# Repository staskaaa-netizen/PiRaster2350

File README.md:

# PiRaster

**PiRaster** is the RP2350/LVDS pixel backend that was written inside uCNC, on
its own: panel timing and scanout, a 4bpp indexed framebuffer, a sixteen-colour
palette, and the drawing primitives every screen is built from. It drives one
panel - a **Sharp LQ121S1LG44**, 800x600, single-channel LVDS, mounted turned a
quarter - and it has been on that panel and no other. The repository is
`PiRaster2350`, after the chip it drives.

It **began as a fork of [PicoLVDS](https://github.com/ceteras/PicoLVDS)**, and
then turned into something much different: what survives from that project is a
handful of its ideas - the HSTX pacer LUT and the way a scanline is packed among
them - while the scanout, the SRAM framebuffer and its palette, the drawing core,
the fonts and the target seam underneath all of it are this project's own. Those
ideas are PicoLVDS's, and the credit for them is that project's.

It was extracted from
`uCNC/src/modules/lvds_renderer` (see *Where this came from* below). The drawing
code, the palette and the fonts are the same code; the hardware half stopped
including `cnc.h` and calls four port hooks instead.

## What you can do with it

Use PiRaster for a **simple panel with a fast and stable picture**:

* **Text where you want it.** `lvds_draw_text(x, y, ...)` writes a string at any
  view coordinate, in three sizes - 6x8 condensed, 8x14, and 8x14 doubled - and
  in any colour of the current palette. Each glyph carries its own background
  colour, because a glyph is filled rectangles. `lvds_draw_text_clip()` writes
  the same text in a fixed number of columns, so the rows of a screen line up
  without the caller measuring anything.
* **A big, cheap screen.** 800x600 is a large work area for text and boxes, and
  a panel of this class costs little. The upright view holds 133 columns by 75
  rows of the 6x8 face, 100 by 42 of the 8x14, and 50 by 21 of the doubled one.
* an operator screen for a machine: text, lines, rectangles and filled
  rectangles in sixteen colours;
* **Motion when you want it.** Lines, rectangles and ellipses animate as well as
  they draw. The sample scene moves a wave, a disc and a gauge from the clock.
  The operator panel is the main job of this path, and motion is the extra.
* a state that you show with a colour, because you can change a palette slot
  while the picture runs;
* a picture that a client makes itself - an emulator, a game, a picture pump -
  because `lvds_target_blit()` takes one row of indices at a time;
* the same picture on a desk, because the host target writes BMP frames and the
  project checks the pixels.

## What you cannot do with it

PiRaster is not a modern display path. Read the limits before you start:

* **Sixteen colours.** The frame uses 4 bits for each pixel. There is no
  blending, no alpha, no anti-aliasing and no image scaling.
* **No video and no photographs.** The path has no decoder and no scaler.
* **One panel and one board.** The geometry, the timing and the clocks are
  compiled in for a Sharp LQ121S1LG44 on an RP2350.
* **No compositor.** There are no layers and no rotation of arbitrary content.

For a modern panel, use its own DSI, eDP or HDMI path.
[docs/when-to-use.md](docs/when-to-use.md) gives the full comparison.

## Features

* **A stable picture.** The default build draws into a PSRAM backbuffer, then
  copies the frame into the scanout buffer. The scanout never reads a
  half-drawn picture.
* **A live palette.** You can re-colour a slot while the picture runs. Everything
  that already uses that colour changes on the next prepared line. You do not
  redraw the screen, and you do not lose a slot.
* **The turn in one place.** The build states the panel mounting one time, in
  `core/lvds_view.h`. Text, lines, rectangles and ellipses then turn with it.
* **A blit call for a client raster.** A client that makes its own rows of
  palette indices draws at row speed, not at pixel speed.
* **A host target.** The same drawing code writes the same picture into a frame
  in RAM, so you can check a layout without a board.
* **Four spare active lines.** The frame carries 604 active lines, not 600. The
  panel shows one line twice at the close of the active area. The four spare
  lines give that repeated line its own place, away from the picture. This is a
  feature of the panel support; the fault behind it is a known issue.
* **Static realtime memory.** The scanout memory is static, aligned and in SRAM.
  The scanout path has no allocator.

## Known issues

* **The panel repeats one line at the close of the active area.** The root cause
  is not known. The four spare active lines hold the repeated line away from the
  picture. **Do not shorten the frame.** The measurements are in
  [LIMITS.md](LIMITS.md). The record is in
  [docs/torture-history.md](docs/torture-history.md).
* **One clock point gives no video.** `420000 / div 3` produces no picture. This
  is a limit of this board. It is not a requirement of the panel.
* **A full redraw costs 33 ms** in the default (double buffered) build. The
  single buffered build costs 3 ms, but the picture tears.
* **The host samples do not run on this bench machine.** Its MinGW gcc cannot
  run its own cc1. The samples compile, and `make run` runs them on a machine
  with a working compiler.

## License

PiRaster is free software under the **GNU General Public License, version 3**
(see [LICENSE](LICENSE)). PiRaster began as a fork of
[PicoLVDS](https://github.com/ceteras/PicoLVDS). That project is also GPL-3.0,
and the ideas that PiRaster keeps from it stay under the same license.

## The boundaries

```
  core/                    device independent. No SDK, no OS, no threads.
    lvds_color.h           a colour: 5-6-5, or a palette slot once a target has one
    lvds_view.h            the view <-> panel turn, stated once
    lvds_canvas.{h,c}      the surface: the only two calls that write, + guards
    lvds_draw.{h,c}        lines, rectangles, ellipses, text (built on those two)
    lvds_palette.{h,c}     the sixteen named colours
    lvds_font*.{h,c}       the two bitmap faces
    lvds_target.h          the seam: what a target implements
  panels/
    sharp_lq121s1lg44.h    geometry, timing, pins and clocks, as data
  targets/
    host/                  the panel on a desk: a 32bpp frame in RAM + a BMP writer
    rp2350/                the panel itself: HSTX, DMA, core1, PSRAM, the port
  samples/
    common/scene.{h,c}     the one picture every sample draws, and the palette banks
    host_loop/             a while loop that draws and writes frames
    host_snapshot/         one frame, checked pixel by pixel - a sample that is a test
    rp2350_panel/          the same picture, on the glass
  lvds_config.h            which panel this build drives
```

Two rules hold the split together:

* **Everything above `lvds_target.h` is portable.** It never mentions DMA, HSTX,
  PSRAM, a pin, or whether the picture ends up on glass or in a file.
* **Everything below it is one panel on one board.** A target writes pixels,
  presents, and owns the palette. It never mentions the view, the turn, the
  palette's names or the drawing primitives.

The documents behind it:

* [docs/architecture.md](docs/architecture.md) - what each layer does with a
  frame, the scanout chain step by step, and the numbers it runs at;
* [docs/boundaries.md](docs/boundaries.md) - who owns what, and why the split is
  where it is;
* [docs/when-to-use.md](docs/when-to-use.md) - what it is good for, what it is
  not, and what to use instead for a modern panel;
* [docs/torture-history.md](docs/torture-history.md) - the stress harness, the
  retired workarounds, and the faults and measurements behind them;
* [LIMITS.md](LIMITS.md) - the hardware limits a consumer has to know before
  using it somewhere new, and what still needs the bench.
* [hardware/](hardware/README.md) - the adapter: its schematic, the KiCad
  project, the fabrication files, and the eight HSTX pins this build drives.

The panel is drawn **upright by default**. A glass bolted turned a quarter -
the machine's own mounting - is one build flag (`-DLVDS_PANEL_TURN=90`, see
`platformio.ini`), and the layout follows it.

**The palette is live.** A colour's name can be redefined while the picture
runs (`lvds_palette_define()`): on the glass the slot it already holds is
re-coloured in place, so everything drawn in that colour changes with it on the
next scanline, with no redraw and no slot churn. `scene_palette_switch()` in the
samples walks four banks to show it.

## Hardware

| what | this build |
| --- | --- |
| glass | Sharp LQ121S1LG44, 800x600, single-channel LVDS: three data pairs and one clock pair |
| board | Waveshare RP2350-PiZero (`-D PICO_BOARD=\"waveshare_rp2350_pizero\"`) |
| HSTX pairs | D0+ D0- D1+ D1- D2+ D2- CLK+ CLK- = GP12, GP13, GP14, GP15, GP16, GP17, GP18, GP19 |
| carrier | the PicoLVDS LVDS adapter, carried in [hardware/](hardware/README.md) |

**There is no LVDS transmitter chip.** The RP2350's HSTX serialiser drives the
panel's four LVDS pairs from those eight pins, in the seven-phase packing that
the pacer LUT produces. That is the idea PiRaster took from PicoLVDS, and it is
the reason this display path is a header of numbers plus one target.

The design of the adapter - schematic, KiCad project and fabrication package -
lives in [hardware/](hardware/README.md), where the project this one came from
keeps it. The eight pins are stated for the firmware in
`panels/sharp_lq121s1lg44.h`, which is the only place the code reads them.

## Build and run

**The host samples need a C compiler and make, nothing else.**

```console
make            # builds both host samples
make run        # builds them, draws three frames, checks one and writes BMPs
```

`samples/host_snapshot/` exits non-zero when a pixel is not where the scene put
it, so `make run` is also a check. The BMPs are written the way the operator
reads the glass: the frame is 800x600 landscape, the picture is 600x800 and
turned, and `host_panel_write_bmp(path, true)` turns it back for you.

**The firmware sample is a PlatformIO project** (`pio run -e rp2350_panel`),
because that is the stack the panel was brought up on; the UF2 lands in
`.pio/build/rp2350_panel/firmware.uf2`. `samples/rp2350_panel/main.cpp` is
Arduino style: `setup()` brings the panel up, and `loop()` draws the scene and
presents it. The framework's own `main()` is `while (1) { loop(); }`, so the
sample adds nothing to it but those calls. The loop paces itself with `millis()`
(`FRAME_MS`, about 50 frames a second), and the drawing itself is a function of
that clock, so the demo behaves the same on every build.

`pio run -e rp2350_panel_fps -t upload` is the same sample with its **frame
meter** in: the loop runs flat out and every sixty frames it prints the
milliseconds a whole frame - clear, scene, present - takes. That is how the
project answers "is this fast enough for a game", on the panel, rather than
guessing from datasheets.

Two meters, because the answer depends on where the draw buffer lives:
`rp2350_panel_fps` uses the double-buffered PSRAM path (the default, and the
machine's), and `rp2350_panel_sram_fps` draws straight into the scanout buffer
for the fast, tearing comparison. A serial terminal must assert DTR
(`pio device monitor` does; a bare port read may not) or the board's output is
dropped.

**The console is the USB serial port, 115200 8N1.** The port appears when the
application runs, and on this bench the application does not run until RESET is
pressed (below). `pio device list` shows its number, and the number can change
between uploads.

```console
pio device list                        # find the port (USB VID:PID 2E8A:...)
pio device monitor -p COM13 -b 115200  # read it
```

The framework drops CDC output until the host asserts DTR, and
`pio device monitor` asserts it. A monitor that is opened after the board has
started would therefore miss the boot lines, so `console_announce()` in the
sample says the state again for each terminal that attaches. `lvds: draw buffer
in psram` is the line to look for; `lvds: the panel did not come up` replaces it
when the bring-up failed.

**A build that prints checks that someone is listening.** The framework's
`Serial` write has nothing to do when no host is attached, so the sample asks
`Serial` (the connected flag) before writing, in both the frame meter and the
port's log hook. What an unwatched write does to this board was *not*
established: a meter build disappearing from the USB bus turned out to be the
reset below, not the write. The announce line follows the same rule: it is
written only while the connected flag is set.

**Flashing on this board: press RESET after the upload.** `pio run -t upload`
does its job - it resets the board into BOOTSEL, writes the image and verifies
it - but the tool's own reboot into the application often does not bring it up
here, and the board sits with no port until the RESET button is pressed. The
board can also drop off the bus with no upload involved at all. The cause is not
established; the measurements, the candidate cause and the recovery checklist
are in [docs/torture-history.md](docs/torture-history.md). One thing is
established: no watchdog inside the firmware can cover that state, because the
firmware is not running in it.

**The default is double buffered on purpose.** Drawing straight into the buffer
the scanout is reading is several times faster, but the panel is looking at the
picture while it is half redrawn - a screen clear per frame reads as a flicker -
which is the lesson LeanCam already learned. Single buffering is an explicit
choice, never the default.

The samples have no RTOS, no tasks, no callbacks and no state machines: draw,
present, repeat. `samples/common/scene.c` is the whole demo, and it is the same
file for the desk and for the glass.

### Native packed-colour builds

`rp2350_panel_4color` runs the original 800x600 PiRaster scene through the
normal core1 and 7x256 LUT scanout, but packs four pixels into each framebuffer
byte:

```console
pio run -e rp2350_panel_4color -t upload
```

All named scene colours map onto black, white, green and blue. The framebuffer
is 120,800 B instead of 241,600 B, and the complete build uses 177,900 B of
RAM with 345,320 B of heap left. The operator saw the native 800x600
four-colour scene run stably on the glass.

Core1 still produces the same seven-phase LVDS words. A 256-entry expansion
table turns each packed 2bpp byte into four nibble indices before the existing
colour LUT. This keeps the unpack work short enough for the scanline deadline.

The green monochrome variant packs eight pixels per byte:

```console
pio run -e rp2350_panel_1bpp -t upload
```

It maps the scene onto black and one green foreground. The framebuffer is
60,400 B and the complete build uses 117,996 B of RAM with 405,224 B of heap
left. A 256-entry table expands each byte directly to all eight nibble indices.
The operator saw the native 800x600 green scene on the glass after the board's
usual post-upload reset.

### CPU-less Command Expander bench

The SRAM-resident line-stream probe works on the glass. It proves that the
HSTX Command Expander can carry the existing raw LVDS words without core1
preparing scanlines.

```console
pio run -e rp2350_panel_headless_sram_bars -t upload
```

The probe bakes three command streams in SRAM: one active colour-bar line, one
blank line, and one VSYNC line. The DMA descriptor ring reuses them for the
frame. The ring has 1,024 entries, so its 354 guard lines lengthen vertical
blanking and lower refresh to about 37 Hz. This is a mechanism probe, not a
panel-timing configuration.

The same mechanism now carries a full-screen, four-colour source:

```console
pio run -e rp2350_panel_headless_200x120 -t upload
```

The source is **200x120**, stored in 12,000 B of SRAM. Every source row is
expanded once through the palette and 7x256 LUT, then nearest-neighbour scaled
4x horizontally and 5x vertically to fill 800x600. Each scaled row is stored as
one complete 925-word scanline, so the 120 rows use 444,000 B. One HSTX-paced
data channel and one descriptor channel loop the rows; core1 remains idle. The
build uses 488,300 B of static RAM, leaving 33,576 B of heap.

Core0 may redraw and rebuild the rows only after descriptor 669. The 354 guard
lines plus the start of vertical blanking give about 9.3 ms, enough for the
four-colour scene at 10 fps. Core1 remains idle. The operator saw the scene
animate on the glass without tearing.

The palette is part of the bake. A colour change does not reach a running
headless stream; the picture must be baked again. The live palette is therefore
lost in this mode.

**`RAW_REPEAT` does not make an LVDS colour line tiny.** A constant-colour
LVDS line still produces seven distinct 32-bit phase windows, and the command
expander repeats one word sequentially. Reordering those seven phases into
seven repeated runs would change the stream. The probe therefore uses complete
`RAW` lines. `RAW_REPEAT` is only correct where a run really consists of
consecutive equal raw words.

The full-frame PSRAM variant is retired:

* its first colour-bar build produced no video;
* a second build produced blinking, never a static frame;
* the working SRAM probe isolates the failure to the PSRAM full-frame loop,
  not the raw LVDS command words.

The scene snapshot was therefore not attempted. The normal core1 path remains
the only supported full-frame scanout. The rollback baseline is the uCNC NCC
image:

```console
pio run -e RP2350-LEANCAM-LVDS-NCC -t upload
```

## What has been verified, and what has not

Verified here:

* `pio run -e rp2350_panel` builds the firmware sample and links it
  (RAM 56.8%, flash 0.4% of 16 MB, `firmware.uf2` generated).
* The normal build is unchanged at RAM 298,156 B and flash 84,824 B after the
  bake API was extracted from the same active-line routine.
* The native four-colour 2bpp build links at RAM 177,900 B and flash 84,760 B.
  The operator saw its 800x600 scene run stably.
* The green 1bpp build links at RAM 117,996 B and flash 84,704 B. The operator
  saw its native 800x600 scene on the glass.
* `rp2350_panel_headless_sram_bars` builds and links at RAM 295,392 B and flash
  70,384 B.
* `rp2350_panel_headless_200x120` builds and links at RAM 488,300 B and flash
  82,992 B.
* The headless ELF has no `core1_entry` or `poll_dma_scanout` symbol.
* The operator saw the SRAM-resident colour bars on the panel with core1 idle.
  This is hardware-verified: the raw Command Expander path and the SRAM line
  reuse work.
* The operator saw the 200x120 four-colour scene full-screen and animating on
  the panel. This hardware-verifies the integer-scaled SRAM line mode and the
  blank-window row rebuild.
* The portable half - core, host target and both host samples - compiles
  warning-free under `-Wall -Wextra` with the toolchain's ARM compiler.

Not verified here:

* **The full-frame PSRAM scanout remains negative.** The 2,479,000-byte loop
  produced no video, then blinking; it never produced a static frame. It stays
  retired.
* **The native-resolution scene comparison was not attempted.** The PSRAM
  scene path failed, and a complete native-resolution scene does not fit the
  SRAM-resident line mechanism. The 200x120 mode is a separate low-resolution
  probe.
* **The host samples have not been run on this machine.** Its MinGW `gcc` cannot
  run its own `cc1` (missing prerequisite DLLs), so any host build fails before
  compiling a line. `make run` is one command away on a machine whose compiler
  works; the check inside `host_snapshot` is what makes that run meaningful.
* The normal demo and the SRAM-resident bars have been on the glass. The
  frame-close tail and the full list of clock points still need their own bench
  checks, listed in `LIMITS.md`.

## Where this came from

`uCNC/src/modules/lvds_renderer` is the same renderer inside uCNC, and the
same directory - module and library, one copy - was published to the
`uCNC-modules` repository. This project is that code rearranged around a target
seam, with the four uCNC calls (`mcu_millis`, `cnc_delay_ms`, `proto_info`,
`cnc_is_file_io_critical`) replaced by `targets/rp2350/rp2350_port.h`.

**The two copies can drift.** They are the same code today; when this project
becomes the owner, the module should be generated from it or replaced by it
rather than edited beside it. That decision has not been made yet.

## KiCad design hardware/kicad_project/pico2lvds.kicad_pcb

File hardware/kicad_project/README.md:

# LVDS adapter

Tested with B089AW01-V.0 and HSD089IFW1-A00-V1.0 on a breadboard.
I'm sure it will work with other displays from old netbooks.

This pcb was not tested yet!

Do NOT build if you're not confident in debugging electronics.
The LVDS cable needs to be hand made, there is no commercially available cable with this layout.
I plan to build mine using the cable from the original netbook, if and when I'll get the pcb ordered.

Good luck!

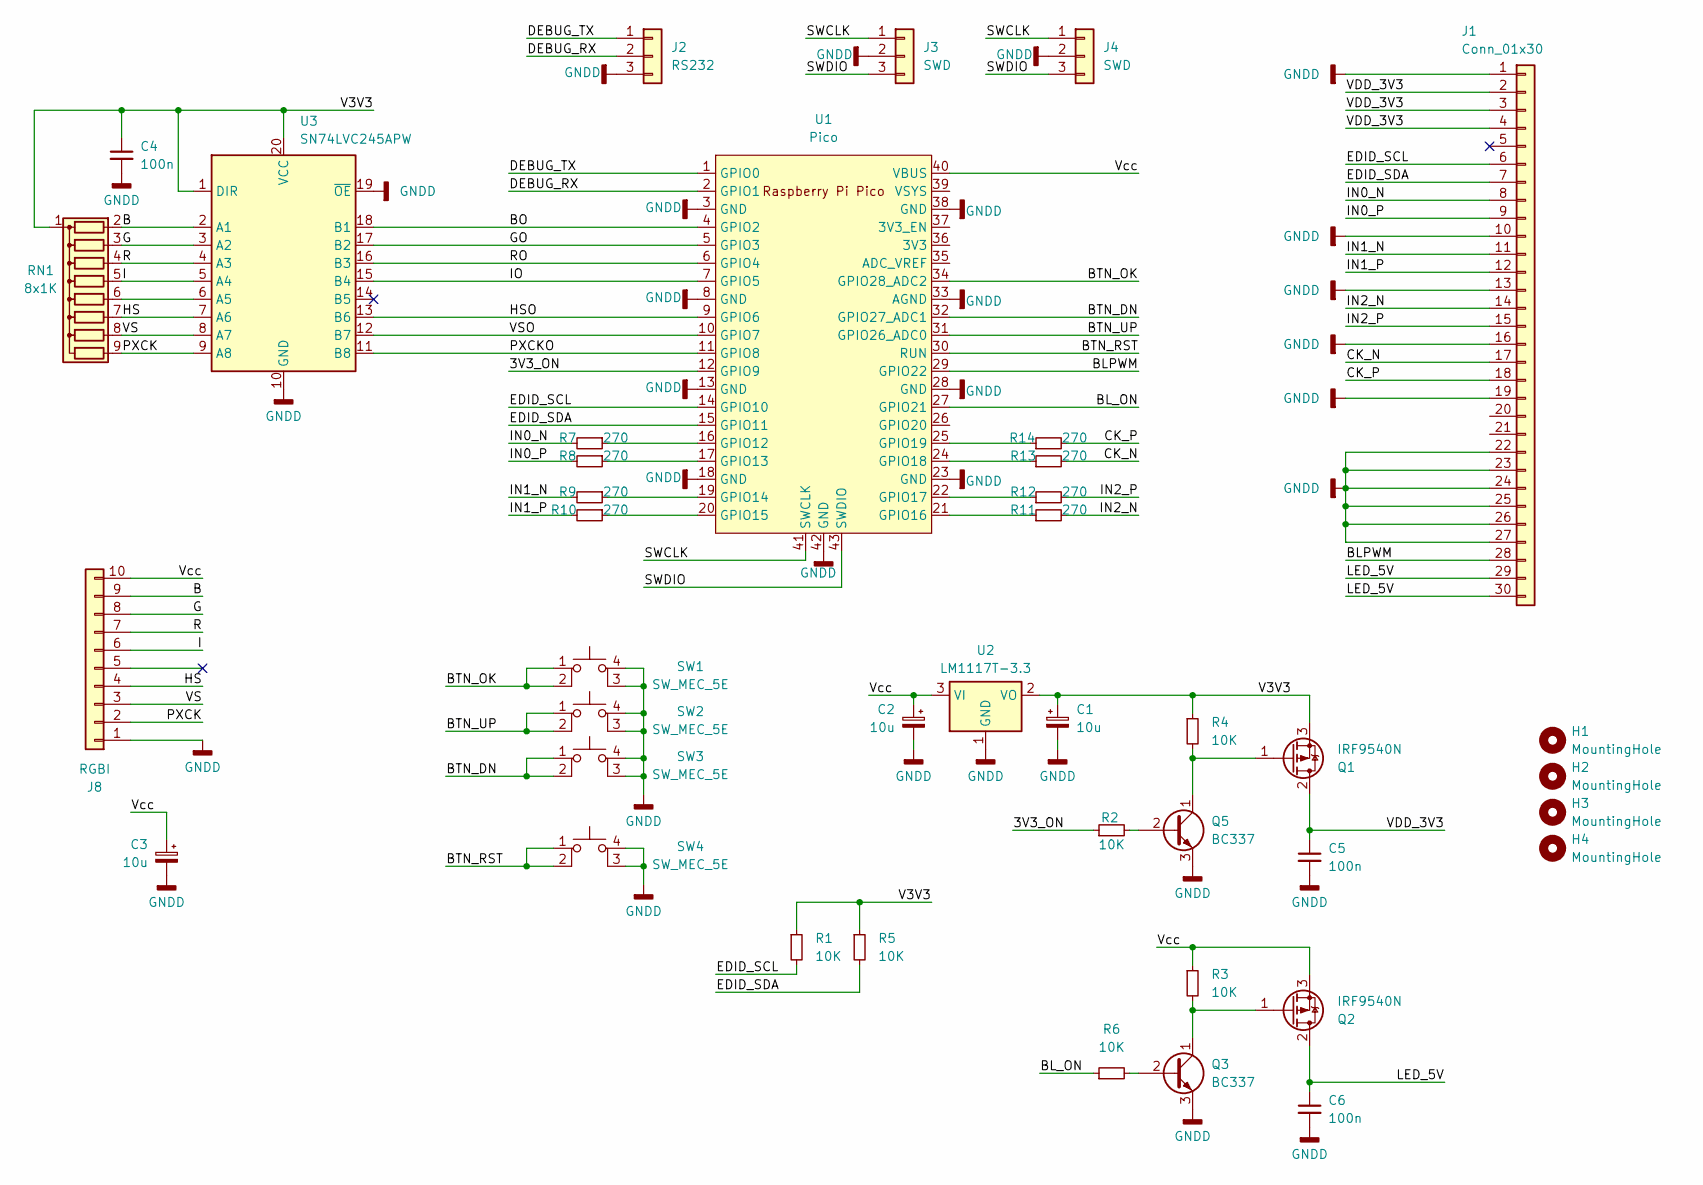
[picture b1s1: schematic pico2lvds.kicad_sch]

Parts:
C1, C2, C3: 10u; CP_Radial_D8.0mm_P5.00mm
C4, C5, C6: 100n; C_Axial_L3.8mm_D2.6mm_P7.50mm_Horizontal
H1, H2, H3, H4: MountingHole; MountingHole_3.2mm_M3
J1: Conn_01x30; Molex_Panelmate_53780-3070_1x30-1MP_P1.25mm_Horizontal
J2: RS232; JST_EH_B3B-EH-A_1x03_P2.50mm_Vertical
J3: SWD; JST_EH_B3B-EH-A_1x03_P2.50mm_Vertical
J4: SWD; JST_GH_BM03B-GHS-TBT_1x03-1MP_P1.25mm_Vertical
J8: RGBI; PinHeader_1x10_P2.54mm_Vertical
Q1, Q2: IRF9540N; TO-220-3_Horizontal_TabDown
Q3, Q5: BC337; TO-92_HandSolder
R1, R2, R3, R4, R5, R6: 10K; R_Axial_DIN0204_L3.6mm_D1.6mm_P7.62mm_Horizontal
R7, R8, R9, R10, R11, R12, R13, R14: 270; R_0805_2012Metric
RN1: 8x1K; R_Array_SIP9
SW1, SW2, SW3, SW4: SW_MEC_5E; SW_PUSH_6mm_1234
U1: Pico; RPi_Pico_SMD_TH_NoS
U2: LM1117T-3.3; TO-220-3_Horizontal_TabDown
U3: SN74LVC245APW; DIP-20_W7.62mm

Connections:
/3V3_ON: R2.1, U1.12 (GPIO9)
/B: J8.9, RN1.2 (R1), U3.2 (A1)
/BLPWM: J1.28, U1.29 (GPIO22)
/BL_ON: R6.1, U1.27 (GPIO21)
/BO: U1.4 (GPIO2), U3.18 (B1)
/BTN_DN: SW3.1, SW3.2, U1.32 (GPIO27_ADC1)
/BTN_OK: SW1.1, SW1.2, U1.34 (GPIO28_ADC2)
/BTN_RST: SW4.1, SW4.2, U1.30 (RUN)
/BTN_UP: SW2.1, SW2.2, U1.31 (GPIO26_ADC0)
/CK_N: J1.17, R13.2
/CK_P: J1.18, R14.2
/DEBUG_RX: J2.2, U1.2 (GPIO1)
/DEBUG_TX: J2.1, U1.1 (GPIO0)
/EDID_SCL: J1.6, R1.2, U1.14 (GPIO10)
/EDID_SDA: J1.7, R5.2, U1.15 (GPIO11)
/G: J8.8, RN1.3 (R2), U3.3 (A2)
/GO: U1.5 (GPIO3), U3.17 (B2)
/HS: J8.4, RN1.7 (R6), U3.7 (A6)
/HSO: U1.9 (GPIO6), U3.13 (B6)
/I: J8.6, RN1.5 (R4), U3.5 (A4)
/IN0_N: J1.8, R7.2
/IN0_P: J1.9, R8.2
/IN1_N: J1.11, R9.2
/IN1_P: J1.12, R10.2
/IN2_N: J1.14, R11.2
/IN2_P: J1.15, R12.2
/IO: U1.7 (GPIO5), U3.15 (B4)
/LED_5V: C6.1, J1.29, J1.30, Q2.2 (D)
/PXCK: J8.2, RN1.9 (R8), U3.9 (A8)
/PXCKO: U1.11 (GPIO8), U3.11 (B8)
/R: J8.7, RN1.4 (R3), U3.4 (A3)
/RO: U1.6 (GPIO4), U3.16 (B3)
/SWCLK: J3.1, J4.1, U1.41 (SWCLK)
/SWDIO: J3.3, J4.3, U1.43 (SWDIO)
/V3V3: C1.1, C4.1, Q1.3 (S), R1.1, R4.1, R5.1, RN1.1 (common), U2.2 (VO), U3.1 (DIR), U3.20 (VCC)
/VDD_3V3: C5.1, J1.2, J1.3, J1.4, Q1.2 (D)
/VS: J8.3, RN1.8 (R7), U3.8 (A7)
/VSO: U1.10 (GPIO7), U3.12 (B7)
/Vcc: C2.1, C3.1, J8.10, Q2.3 (S), R3.1, U1.40 (VBUS), U2.3 (VI)
GNDD: C1.2, C2.2, C3.2, C4.2, C5.2, C6.2, J1.1, J1.10, J1.13, J1.16, J1.19, J1.22, J1.23, J1.24, J1.25, J1.26, J1.27, J2.3, J3.2, J4.2, J8.1, Q3.3 (E), Q5.3 (E), SW1.3 (K), SW1.4 (A), SW2.3 (K), SW2.4 (A), SW3.3 (K), SW3.4 (A), SW4.3 (K), SW4.4 (A), U1.3 (GND), U1.8 (GND), U1.13 (GND), U1.18 (GND), U1.23 (GND), U1.28 (GND), U1.33 (AGND), U1.38 (GND), U1.42 (GND), U2.1 (GND), U3.10 (GND), U3.19 (~OE)
unnamed: Q1.1 (G), Q5.1 (C), R4.2
unnamed: Q2.1 (G), Q3.1 (C), R3.2
unnamed: Q3.2 (B), R6.2
unnamed: Q5.2 (B), R2.2
unnamed: RN1.6 (R5), U3.6 (A5)
unnamed: R7.1, U1.16 (GPIO12)
unnamed: R8.1, U1.17 (GPIO13)
unnamed: R9.1, U1.19 (GPIO14)
unnamed: R10.1, U1.20 (GPIO15)
unnamed: R11.1, U1.21 (GPIO16)
unnamed: R12.1, U1.22 (GPIO17)
unnamed: R13.1, U1.24 (GPIO18)
unnamed: R14.1, U1.25 (GPIO19)

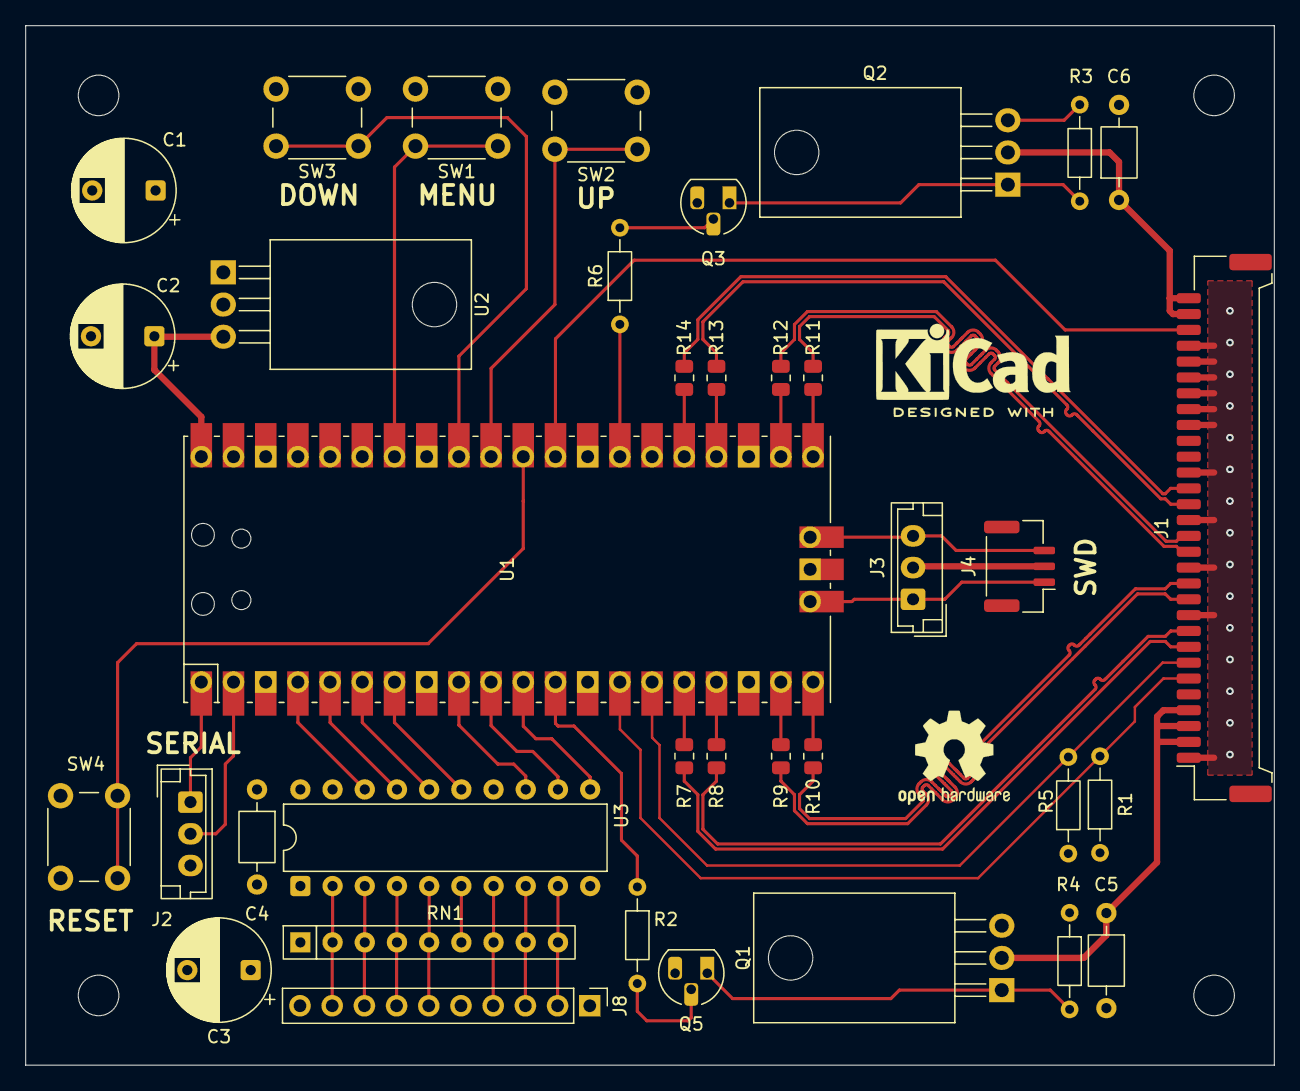
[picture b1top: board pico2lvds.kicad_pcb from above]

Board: 4 copper layers, 98.5 x 82.0 mm, 41 parts (0 on the bottom side), 53 nets.
